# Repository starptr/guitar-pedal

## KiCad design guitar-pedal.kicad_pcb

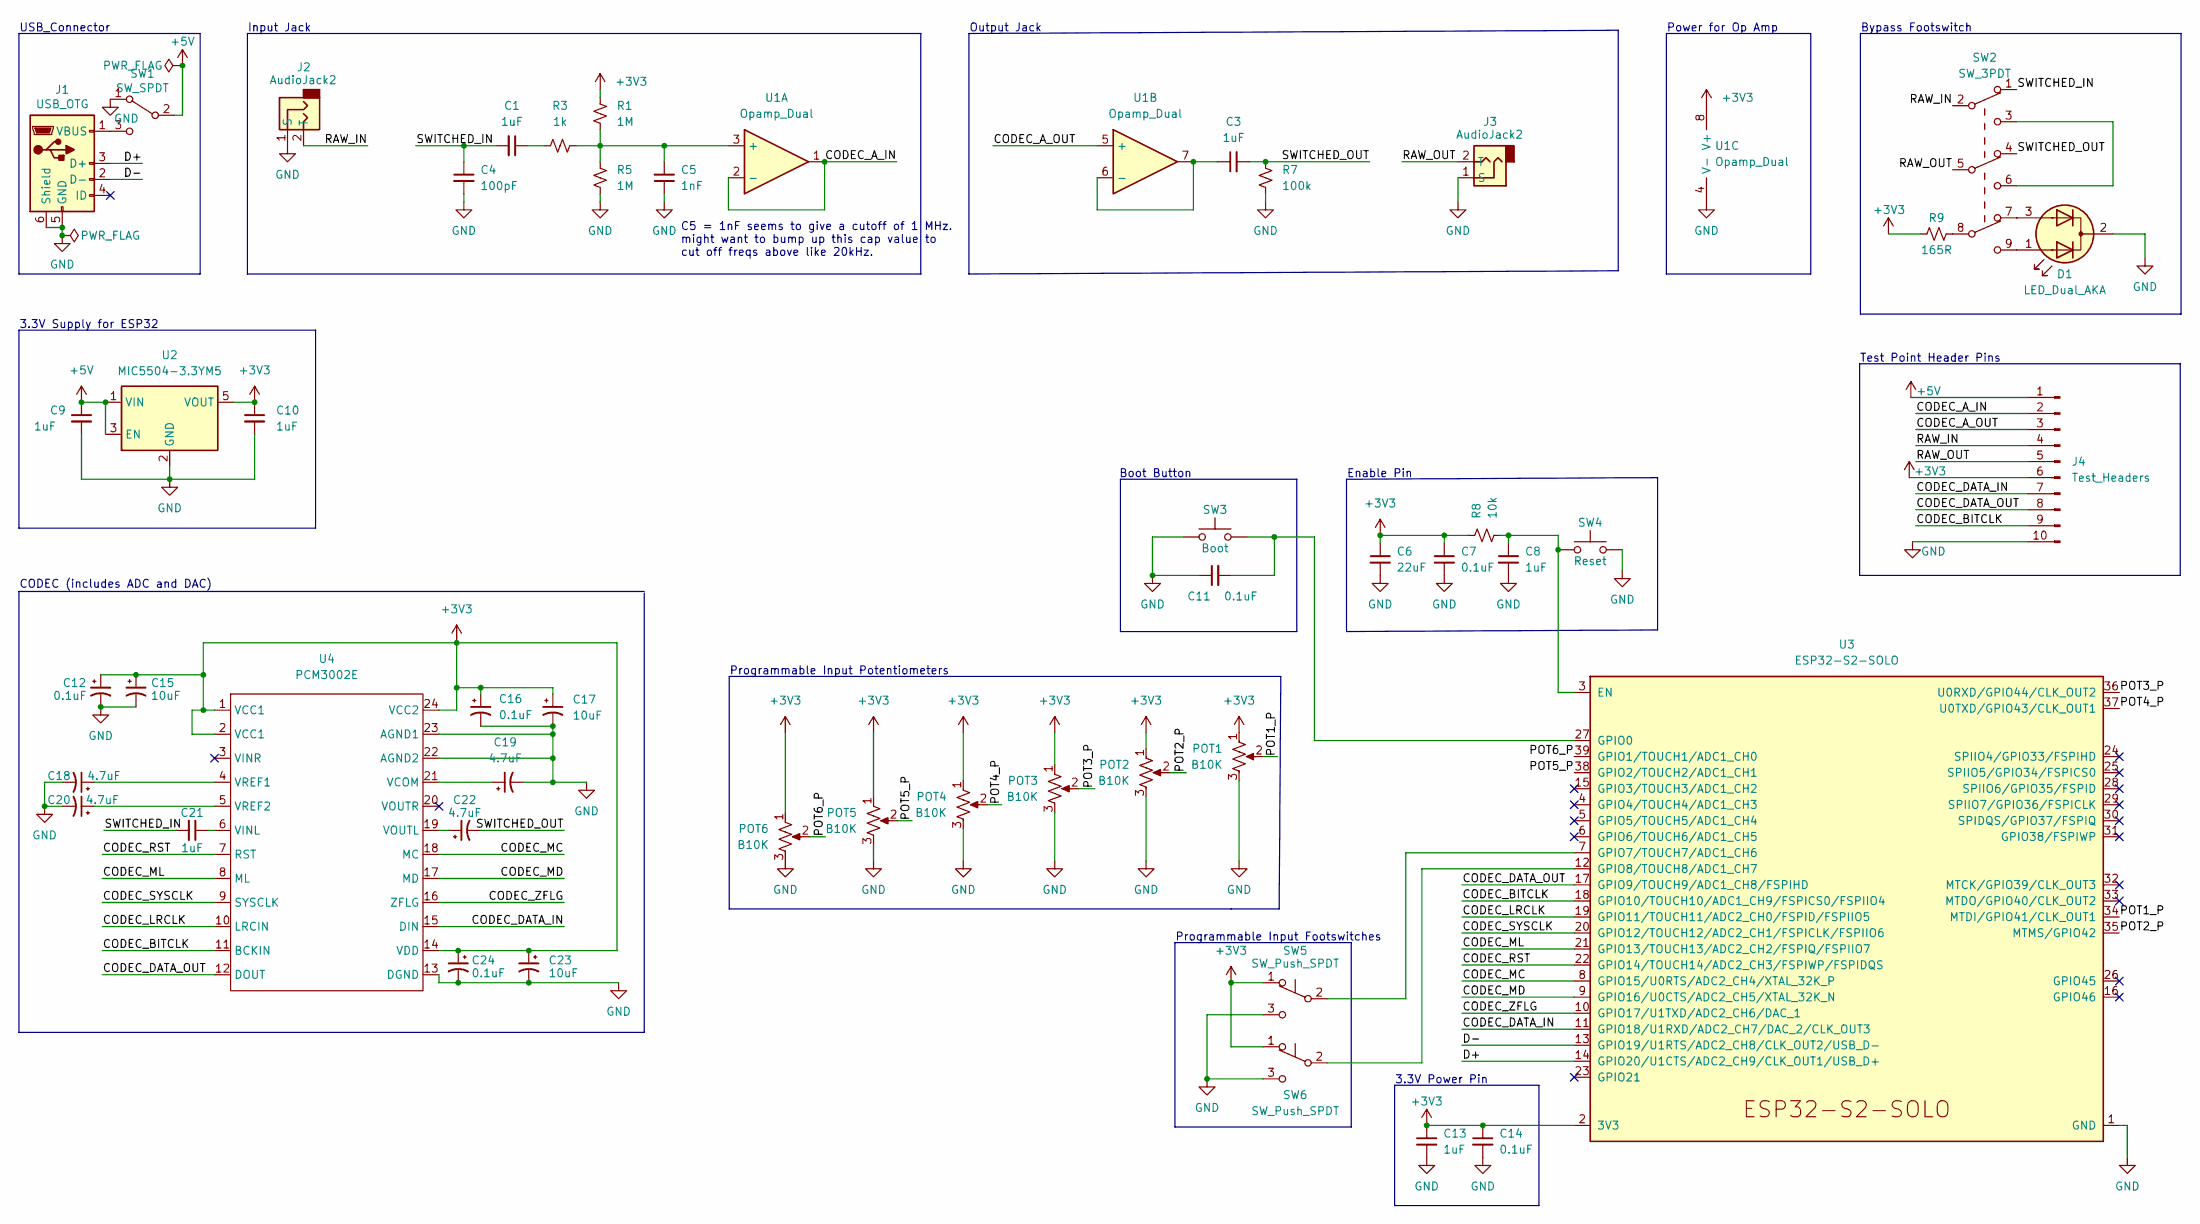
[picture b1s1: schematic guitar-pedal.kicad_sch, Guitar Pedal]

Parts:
C1, C3, C8, C9, C10, C13, C21: 1uF; C_0603_1608Metric_Pad1.08x0.95mm_HandSolder
C4: 100pF; C_0603_1608Metric_Pad1.08x0.95mm_HandSolder
C5: 1nF; C_0603_1608Metric_Pad1.08x0.95mm_HandSolder
C6: 22uF; C_0805_2012Metric_Pad1.18x1.45mm_HandSolder
C7, C11, C12, C14, C16, C24: 0.1uF; C_0603_1608Metric_Pad1.08x0.95mm_HandSolder
C15, C17, C23: 10uF; C_0805_2012Metric_Pad1.18x1.45mm_HandSolder
C18, C19, C20, C22: 4.7uF; C_0603_1608Metric_Pad1.08x0.95mm_HandSolder
D1: LED_Dual_AKA; PinHeader_1x03_P2.54mm_Vertical
J1: USB_OTG; USB_Micro-B_Molex-105017-0001
J2, J3: AudioJack2; PinHeader_1x02_P2.54mm_Vertical
J4: Test_Headers; PinHeader_2x05_P2.54mm_Vertical
POT1, POT2, POT3, POT4, POT5, POT6: B10K; PinHeader_1x03_P2.54mm_Vertical
R1, R5: 1M; R_0603_1608Metric_Pad0.98x0.95mm_HandSolder
R3: 1k; R_0603_1608Metric_Pad0.98x0.95mm_HandSolder
R7: 100k; R_0603_1608Metric_Pad0.98x0.95mm_HandSolder
R8: 10k; R_0805_2012Metric_Pad1.20x1.40mm_HandSolder
R9: 165R; R_0603_1608Metric_Pad0.98x0.95mm_HandSolder
SW1: SW_SPDT; PinHeader_1x03_P2.54mm_Vertical
SW2: SW_3PDT; PinHeader_1x09_P2.54mm_Vertical
SW3: Boot; PinHeader_1x02_P2.54mm_Vertical
SW4: Reset; PinHeader_1x02_P2.54mm_Vertical
SW5, SW6: SW_Push_SPDT; PinHeader_1x03_P2.54mm_Vertical
U1: Opamp_Dual; PW8
U2: MIC5504-3.3YM5; SOT-23-5
U3: ESP32-S2-SOLO
U4: PCM3002E

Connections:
+3V3: C6.1, C7.1, C10.1, C12.1, C13.1, C14.1, C15.1, C16.1, C17.1, C23.1, C24.1, J4.6, POT1.1, POT2.1, POT3.1, POT4.1, POT5.1, POT6.1, R1.2, R8.1, R9.1, SW5.1 (A), SW6.1 (A), U1.8 (V+), U2.5 (VOUT), U3.2 (3V3), U4.1 (VCC1), U4.2 (VCC1), U4.14 (VDD), U4.24 (VCC2)
+5V: C9.1, J4.1, SW1.2 (B), U2.1 (VIN), U2.3 (EN)
/CODEC_A_IN: J4.2, U1.1, U1.2 (-)
/CODEC_A_OUT: J4.3, U1.5 (+)
/CODEC_BITCLK: J4.9, U3.18 (GPIO10/TOUCH10/ADC1_CH9/FSPICS0/FSPIIO4), U4.11 (BCKIN)
/CODEC_DATA_IN: J4.7, U3.11 (GPIO18/U1RXD/ADC2_CH7/DAC_2/CLK_OUT3), U4.15 (DIN)
/CODEC_DATA_OUT: J4.8, U3.17 (GPIO9/TOUCH9/ADC1_CH8/FSPIHD), U4.12 (DOUT)
/CODEC_LRCLK: U3.19 (GPIO11/TOUCH11/ADC2_CH0/FSPID/FSPIIO5), U4.10 (LRCIN)
/CODEC_MC: U3.8 (GPIO15/U0RTS/ADC2_CH4/XTAL_32K_P), U4.18 (MC)
/CODEC_MD: U3.9 (GPIO16/U0CTS/ADC2_CH5/XTAL_32K_N), U4.17 (MD)
/CODEC_ML: U3.21 (GPIO13/TOUCH13/ADC2_CH2/FSPIQ/FSPIIO7), U4.8 (ML)
/CODEC_RST: U3.22 (GPIO14/TOUCH14/ADC2_CH3/FSPIWP/FSPIDQS), U4.7 (RST)
/CODEC_SYSCLK: U3.20 (GPIO12/TOUCH12/ADC2_CH1/FSPICLK/FSPIIO6), U4.9 (SYSCLK)
/CODEC_ZFLG: U3.10 (GPIO17/U1TXD/ADC2_CH6/DAC_1), U4.16 (ZFLG)
/D+: J1.3 (D+), U3.14 (GPIO20/U1CTS/ADC2_CH9/CLK_OUT1/USB_D+)
/D-: J1.2 (D-), U3.13 (GPIO19/U1RTS/ADC2_CH8/CLK_OUT2/USB_D-)
/POT1_P: POT1.2, U3.34 (MTDI/GPIO41/CLK_OUT1)
/POT2_P: POT2.2, U3.35 (MTMS/GPIO42)
/POT3_P: POT3.2, U3.36 (U0RXD/GPIO44/CLK_OUT2)
/POT4_P: POT4.2, U3.37 (U0TXD/GPIO43/CLK_OUT1)
/POT5_P: POT5.2, U3.38 (GPIO2/TOUCH2/ADC1_CH1)
/POT6_P: POT6.2, U3.39 (GPIO1/TOUCH1/ADC1_CH0)
/RAW_IN: J2.2 (T), J4.4, SW2.2
/RAW_OUT: J3.2 (T), J4.5, SW2.5
/SWITCHED_IN: C1.2, C4.1, C21.2, SW2.1
/SWITCHED_OUT: C3.2, C22.2, R7.2, SW2.4
GND: C4.2, C5.1, C6.2, C7.2, C8.2, C9.2, C10.2, C11.1, C12.2, C13.2, C14.2, C15.2, C16.2, C17.2, C18.2, C19.2, C20.2, C23.2, C24.2, D1.2 (K), J1.5 (GND), J1.6 (Shield), J2.1 (S), J3.1 (S), J4.10, POT1.3, POT2.3, POT3.3, POT4.3, POT5.3, POT6.3, R5.1, R7.1, SW1.1 (A), SW3.1, SW4.2, SW5.3 (C), SW6.3 (C), U1.4 (V-), U2.2 (GND), U3.1 (GND), U3.40 (GND), U3.41 (GND), U4.13 (DGND), U4.22 (AGND2), U4.23 (AGND1)
unnamed: C1.1, R3.1
unnamed: C3.1, U1.6 (-), U1.7
unnamed: C5.2, R1.1, R3.2, R5.2, U1.3 (+)
unnamed: C8.1, R8.2, SW4.1, U3.3 (EN)
unnamed: C11.2, SW3.2, U3.27 (GPIO0)
unnamed: C18.1, U4.4 (VREF1)
unnamed: C19.1, U4.21 (VCOM)
unnamed: C20.1, U4.5 (VREF2)
unnamed: C21.1, U4.6 (VINL)
unnamed: C22.1, U4.19 (VOUTL)
unnamed: D1.1 (A1), SW2.9
unnamed: D1.3 (A2), SW2.7
unnamed: J1.1 (VBUS), SW1.3 (C)
unnamed: R9.2, SW2.8
unnamed: SW2.3, SW2.6
unnamed: SW5.2 (B), U3.7 (GPIO7/TOUCH7/ADC1_CH6)
unnamed: SW6.2 (B), U3.12 (GPIO8/TOUCH8/ADC1_CH7)

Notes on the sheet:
3.3V Supply for ESP32
USB_Connector
Power for Op Amp
3.3V Power Pin
Bypass Footswitch
Boot Button
Programmable Input Footswitches
CODEC (includes ADC and DAC)
Test Point Header Pins
Enable Pin
Output Jack
Input Jack
C5 = 1nF seems to give a cutoff of 1 MHz. might want to bump up this cap value to cut off freqs above like 20kHz.
Programmable Input Potentiometers

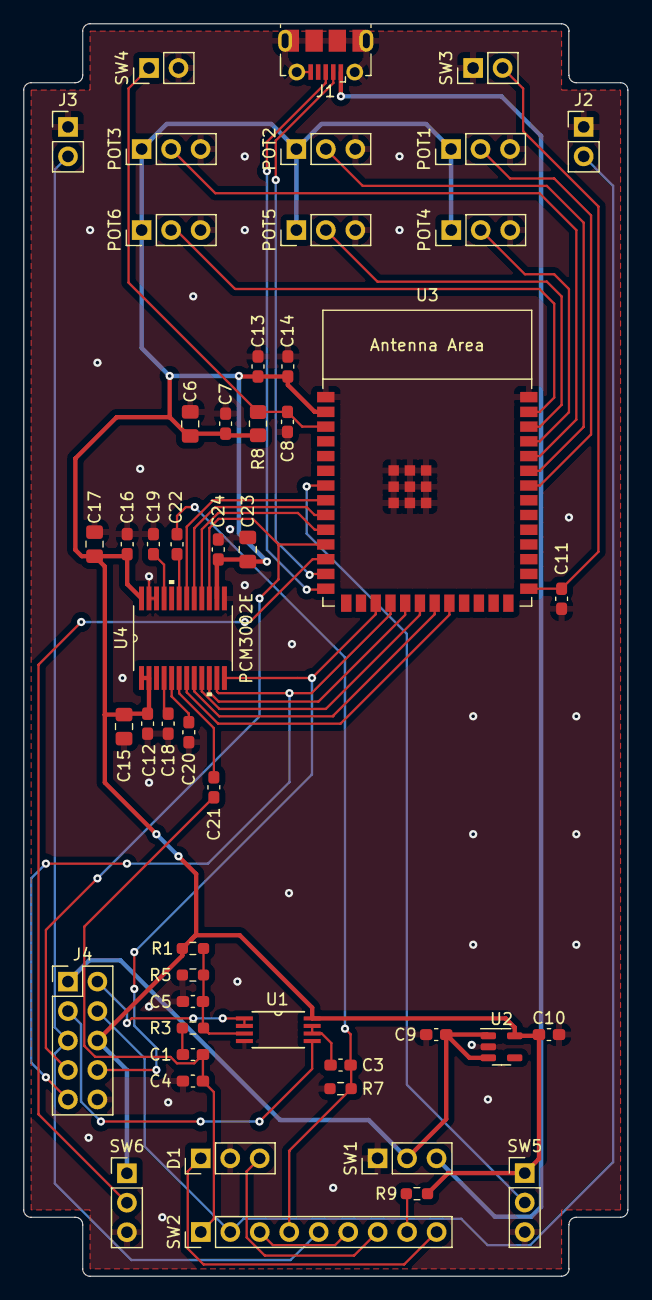
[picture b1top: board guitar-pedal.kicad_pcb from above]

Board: 2 copper layers, 52.1 x 107.9 mm, 50 parts (0 on the bottom side), 44 nets.

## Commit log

2023-03-18 Ignore macos-related files
2023-03-21 first draft of schematic
2023-04-03 replace GNDREF with GND; and Reset and Boot switches; prepare to change 9V->3.3V LDO with 5V->3.3V
2023-04-03 import course DRC settings and net classes
2023-04-04 add test points
2023-04-04 Update gitignore
2023-04-04 Add pcm3002e symbol
2023-04-04 remove 9V supply and fix value suffixes
2023-04-05 pre-design review tweaks
2023-04-07 create ES8374 codec symbol
2023-04-07 add ES8374 codec to schematic and start wiring its pins
2023-04-10 poop
2023-04-11 figured out pre-and post processing (mostly) and removed ES8374 codec to go back to just PCM3002
2023-04-11 add missing letter F from capacitor value
2023-04-11 some reorganization
2023-04-14 assign footprints and fix a couple small things
2023-04-14 getting started on layout
2023-04-14 no seriously, get started on layout
2023-04-15 wip traces and layout
2023-04-15 slight layout progress
2023-04-15 Reassign potentiometer pins to esp32
2023-04-15 layout: wired pots sort of
2023-04-16 layout progress!
2023-04-16 tiny changes
2023-04-16 Finish tracing
2023-04-17 fix self-intersecting courtyard of codec footprint
2023-04-17 start ground pour
2023-04-17 done with layout submission :O
2023-04-18 add back silkscreen
2023-04-18 Fix switch to ground
2023-04-18 Change trace width, move usb
2023-04-18 silkscreen art (redone)

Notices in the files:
parts and their libraries:
Copyright 2021 Accelerated Designs. All rights reserved.
